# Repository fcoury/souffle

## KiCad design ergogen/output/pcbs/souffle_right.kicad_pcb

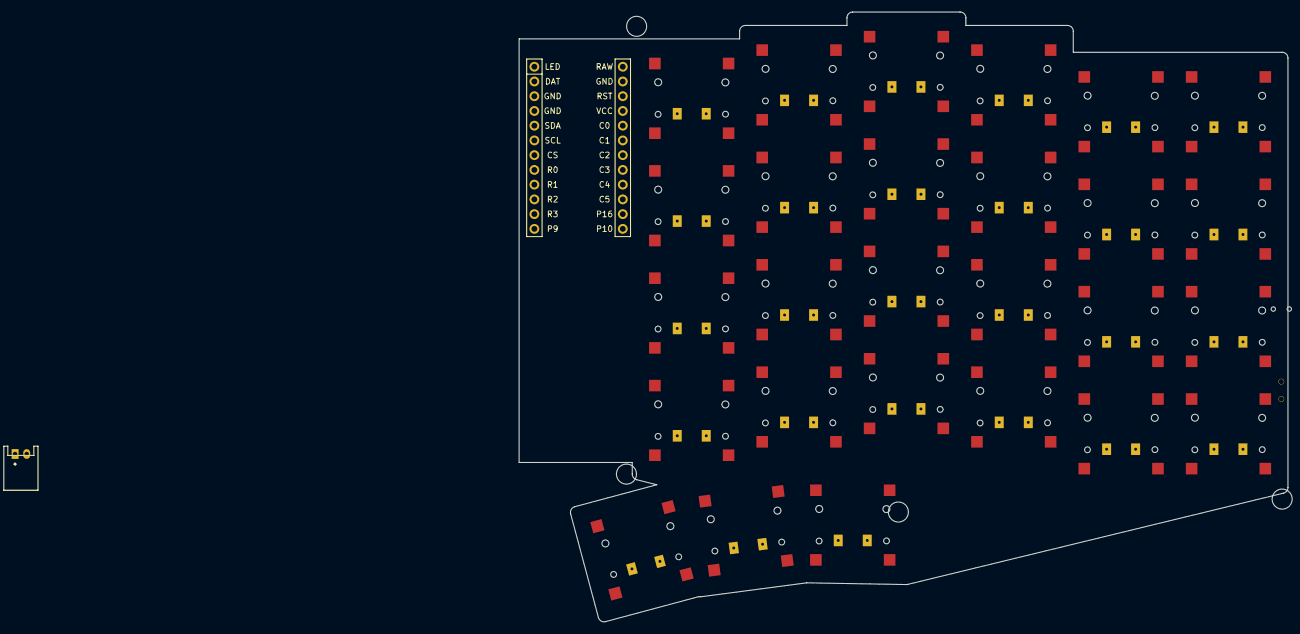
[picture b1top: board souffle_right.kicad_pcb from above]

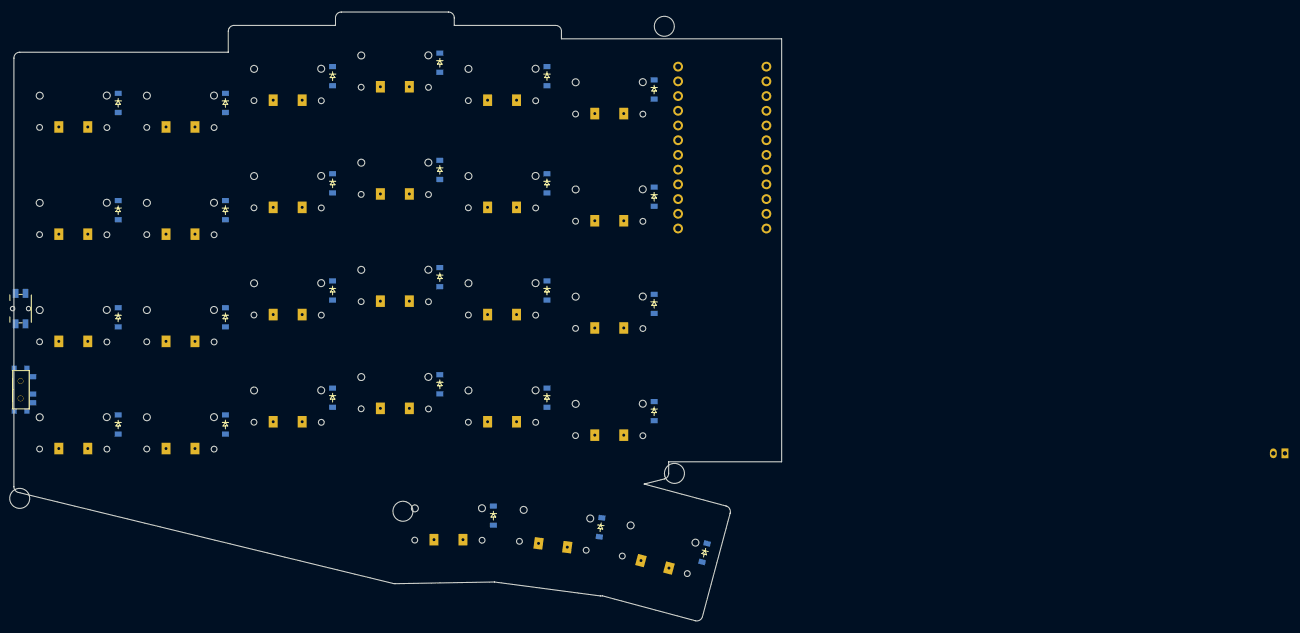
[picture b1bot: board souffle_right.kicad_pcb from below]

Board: 2 copper layers, 132.5 x 105.1 mm, 62 parts (27 on the bottom side), 41 nets, no tracks yet.

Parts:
B1: Panasonic_EVQPUL_EVQPUC
D1, D2, D3, D4, D5, D6, D7, D8, D9, D10, D11, D12, D13, D14, D15, D16, D17, D18, D19, D20, D21, D22, D23, D24, D25, D26, D27: diode_tht_sod123
JST1: JST_PH_S2B-PH-K_02x2.00mm_Angled
MCU1: mcu_nice_nano
MH1, MH2, MH3, MH4: mounting_hole_npth
S1, S2, S3, S4, S5, S6, S7, S8, S9, S10, S11, S12, S13, S14, S15, S16, S17, S18, S19, S20, S21, S22, S23, S24, S25, S26, S27: CPG1316S01D02
T1: SPDT_C128955

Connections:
C0: MCU1.5, S1.1, S2.1, S3.1, S4.1
C1: MCU1.6, S5.1, S6.1, S7.1, S8.1
C2: MCU1.7, S9.1, S10.1, S11.1, S12.1
C3: MCU1.8, S13.1, S14.1, S15.1, S16.1, S25.1
C4: MCU1.9, S17.1, S18.1, S19.1, S20.1, S26.1
C5: MCU1.10, S21.1, S22.1, S23.1, S24.1, S27.1
GND: B1.1, JST1.2, MCU1.2, MCU1.21, MCU1.22
R0: D4.1, D8.1, D12.1, D16.1, D20.1, D24.1, MCU1.17
R1: D3.1, D7.1, D11.1, D15.1, D19.1, D23.1, MCU1.16
R2: D2.1, D6.1, D10.1, D14.1, D18.1, D22.1, MCU1.15
R3: D1.1, D5.1, D9.1, D13.1, D17.1, D21.1, MCU1.14
R4: D25.1, D26.1, D27.1
RAW: MCU1.1, T1.2
RST: B1.2, MCU1.3
mirror_index_bottom: D17.2, S17.2
mirror_index_home: D18.2, S18.2
mirror_index_number: D20.2, S20.2
mirror_index_top: D19.2, S19.2
mirror_inner_bottom: D21.2, S21.2
mirror_inner_home: D22.2, S22.2
mirror_inner_number: D24.2, S24.2
mirror_inner_top: D23.2, S23.2
mirror_inward_home: D25.2, S25.2
mirror_middle_bottom: D13.2, S13.2
mirror_middle_home: D14.2, D26.2, S14.2, S26.2
mirror_middle_number: D16.2, S16.2
mirror_middle_top: D15.2, S15.2
mirror_outer_bottom: D1.2, S1.2
mirror_outer_home: D2.2, S2.2
mirror_outer_number: D4.2, S4.2
mirror_outer_top: D3.2, S3.2
mirror_outward_home: D27.2, S27.2
mirror_pinky_bottom: D5.2, S5.2
mirror_pinky_home: D6.2, S6.2
mirror_pinky_number: D8.2, S8.2
mirror_pinky_top: D7.2, S7.2
mirror_ring_bottom: D9.2, S9.2
mirror_ring_home: D10.2, S10.2
mirror_ring_number: D12.2, S12.2
mirror_ring_top: D11.2, S11.2
pos: JST1.1, T1.1

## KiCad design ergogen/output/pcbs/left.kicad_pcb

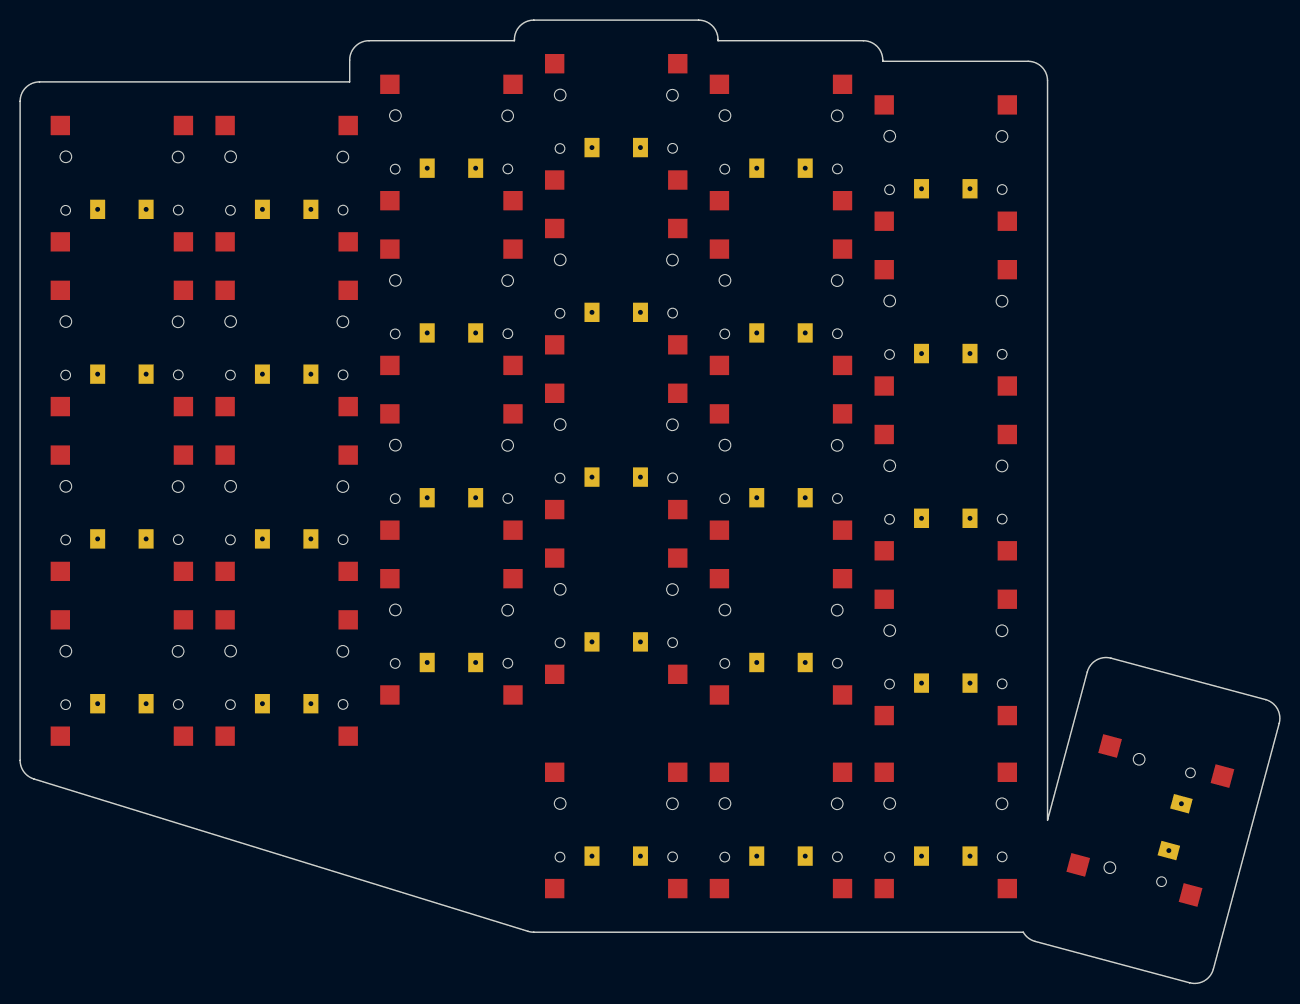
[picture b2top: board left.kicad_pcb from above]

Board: 2 copper layers, 130.0 x 99.4 mm, 28 parts (0 on the bottom side), 6 nets, no tracks yet.

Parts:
S1, S2, S3, S4, S5, S6, S7, S8, S9, S10, S11, S12, S13, S14, S15, S16, S17, S18, S19, S20, S21, S22, S23, S24, S25, S26, S27, S28: CPG1316S01D02_reversible

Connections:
C0: S1.1, S2.1, S3.1, S4.1
C1: S5.1, S6.1, S7.1, S8.1
C2: S9.1, S10.1, S11.1, S12.1, S25.1
C3: S13.1, S14.1, S15.1, S16.1, S26.1
C4: S17.1, S18.1, S19.1, S20.1, S27.1
C5: S21.1, S22.1, S23.1, S24.1, S28.1

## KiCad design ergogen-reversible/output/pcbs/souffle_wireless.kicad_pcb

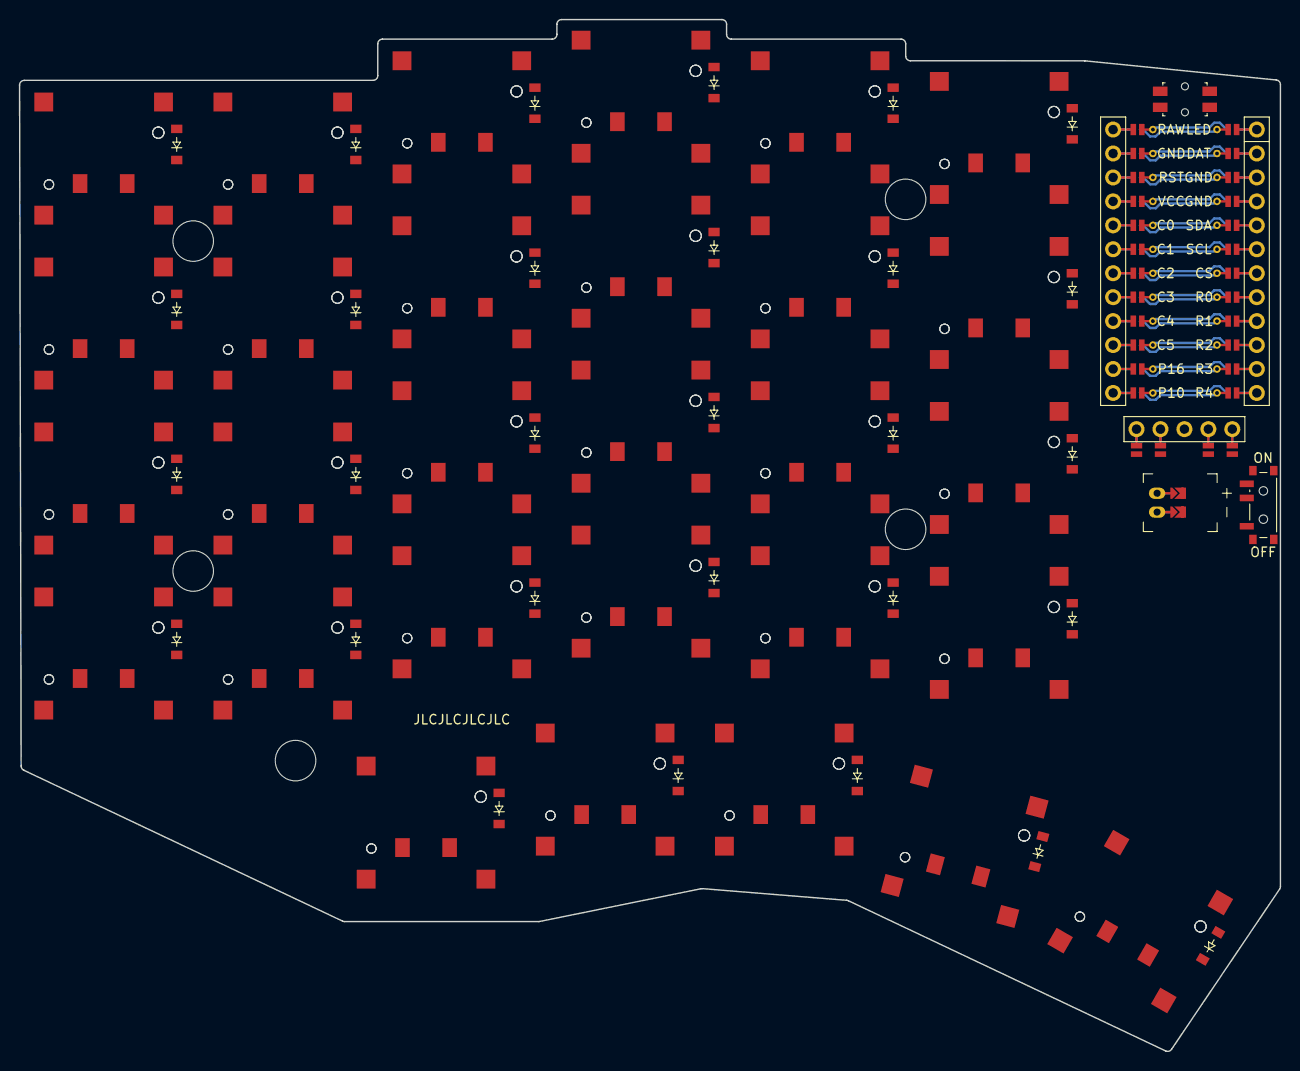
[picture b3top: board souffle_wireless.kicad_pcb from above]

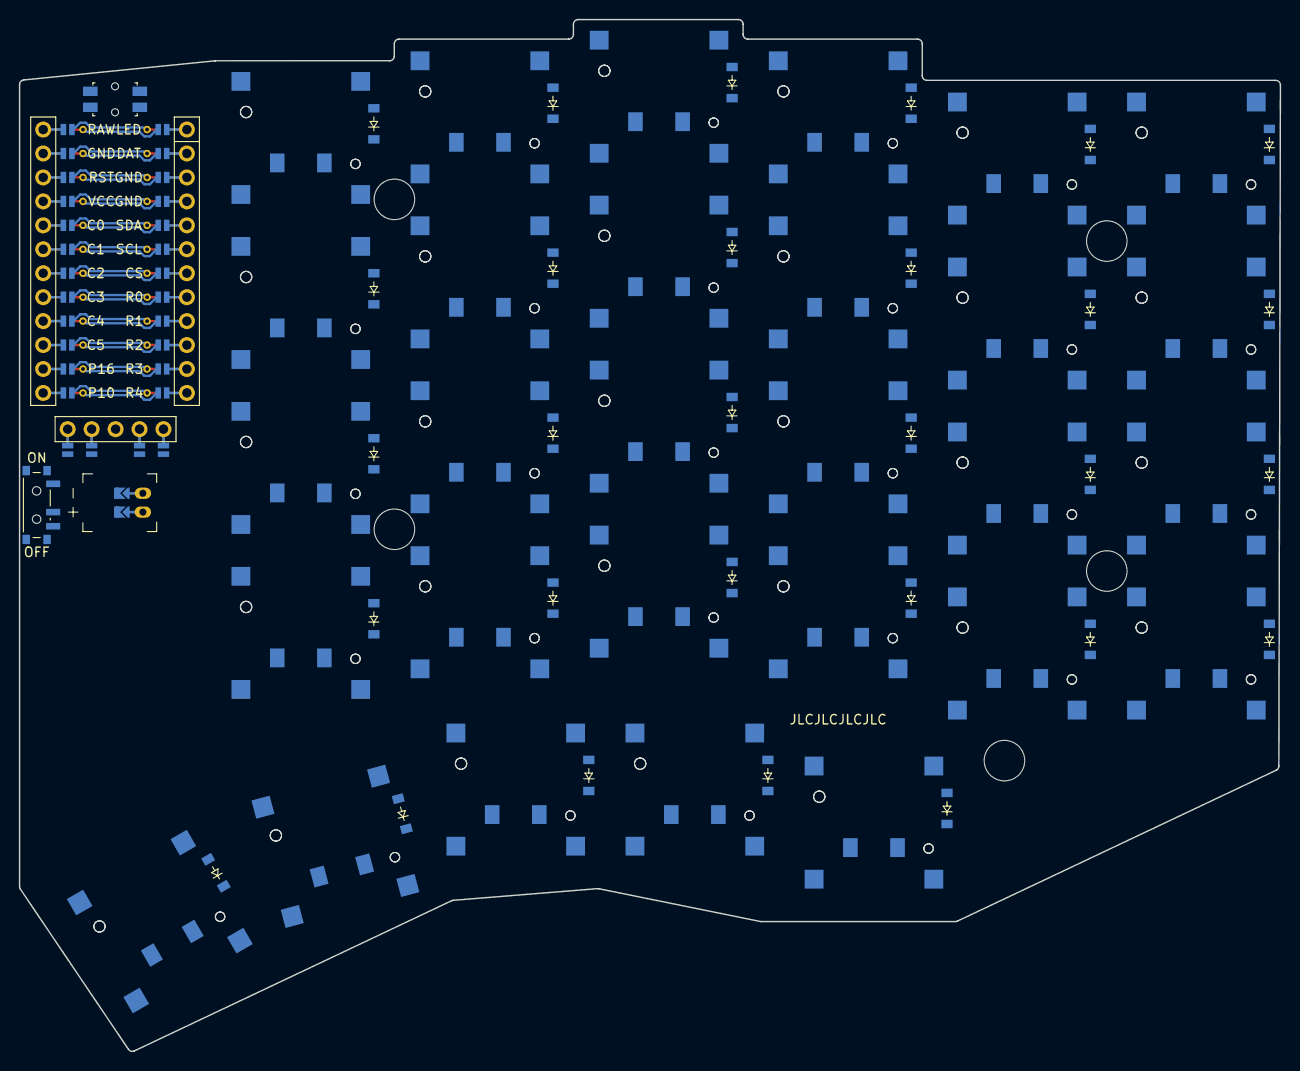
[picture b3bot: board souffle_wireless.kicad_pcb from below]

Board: 2 copper layers, 133.8 x 109.5 mm, 126 parts (58 on the bottom side), 83 nets.

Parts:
D1, D2, D3, D4, D5, D6, D7, D8, D9, D10, D11, D12, D13, D14, D15, D16, D17, D18, D19, D20, D21, D22, D23, D24, D25, D26, D27, D28, D29, D30, D31, D32, D33, D34, D35, D36, D37, D38, D39, D40, D41, D42, D43, D44, D45, D46, D47, D48, D49, D50, D51, D52, D53, D54, D55, D56, D57, D58: diode_tht_sod123
DISP1: display_nice_view
JST1: battery_connector_jst_ph_2
MCU1: mcu_nice_nano
MH1, MH2, MH3, MH4, MH5: mounting_hole_npth
PWR1: power_switch_smd_side
RST1: reset_switch_smd_side
S1, S2, S3, S4, S5, S6, S7, S8, S9, S10, S11, S12, S13, S14, S15, S16, S17, S18, S19, S20, S21, S22, S23, S24, S25, S26, S27, S28, S29, S30, S31, S32, S33, S34, S35, S36, S37, S38, S39, S40, S41, S42, S43, S44, S45, S46, S47, S48, S49, S50, S51, S52, S53, S54, S55, S56, S57, S58: CPG1316S01D02_mikeholscher

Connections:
BAT_P: JST1.1, PWR1.1, PWR1.3
C0: MCU1.120, S1.2, S2.2, S3.2, S4.2, S30.2, S31.2, S32.2, S33.2
C1: MCU1.119, S5.2, S6.2, S7.2, S8.2, S25.2, S34.2, S35.2, S36.2, S37.2, S54.2
C2: MCU1.118, S9.2, S10.2, S11.2, S12.2, S26.2, S38.2, S39.2, S40.2, S41.2, S55.2
C3: MCU1.117, S13.2, S14.2, S15.2, S16.2, S27.2, S42.2, S43.2, S44.2, S45.2, S56.2
C4: MCU1.116, S17.2, S18.2, S19.2, S20.2, S28.2, S46.2, S47.2, S48.2, S49.2, S57.2
C5: MCU1.115, S21.2, S22.2, S23.2, S24.2, S29.2, S50.2, S51.2, S52.2, S53.2, S58.2
CS: DISP1.10, DISP1.20, MCU1.107
DISP1_1: DISP1.1, DISP1.14, DISP1.27
DISP1_2: DISP1.2, DISP1.15, DISP1.26
DISP1_4: DISP1.4, DISP1.16, DISP1.25
DISP1_5: DISP1.5, DISP1.17, DISP1.24
GND: DISP1.11, DISP1.21, JST1.2, MCU1.103, MCU1.104, MCU1.123, RST1.1, RST1.3
JST1_1: JST1.11, JST1.21, JST1.31
JST1_2: JST1.12, JST1.22, JST1.32
R0: D4.1, D8.1, D12.1, D16.1, D20.1, D24.1, D33.1, D37.1, D41.1, D45.1, D49.1, D53.1, MCU1.108
R1: D3.1, D7.1, D11.1, D15.1, D19.1, D23.1, D32.1, D36.1, D40.1, D44.1, D48.1, D52.1, MCU1.109
R2: D2.1, D6.1, D10.1, D14.1, D18.1, D22.1, D31.1, D35.1, D39.1, D43.1, D47.1, D51.1, MCU1.110
R3: D1.1, D5.1, D9.1, D13.1, D17.1, D21.1, D30.1, D34.1, D38.1, D42.1, D46.1, D50.1, MCU1.111
R4: D25.1, D26.1, D27.1, D28.1, D29.1, D54.1, D55.1, D56.1, D57.1, D58.1, MCU1.112
RAW: MCU1.124, PWR1.2
RST: MCU1.122, RST1.2, RST1.4
SCL: DISP1.12, DISP1.22, MCU1.106
SDA: DISP1.13, DISP1.23, MCU1.105
VCC: DISP1.3, MCU1.121
big_outward_home_B: D29.2, S29.1
big_outward_home_F: D58.2, S58.1
extra_outward_home_B: D28.2, S28.1
extra_outward_home_F: D57.2, S57.1
index_bottom_B: D17.2, S17.1
index_bottom_F: D46.2, S46.1
index_home_B: D18.2, S18.1
index_home_F: D47.2, S47.1
index_number_B: D20.2, S20.1
index_number_F: D49.2, S49.1
index_top_B: D19.2, S19.1
index_top_F: D48.2, S48.1
inner_bottom_B: D21.2, S21.1
inner_bottom_F: D50.2, S50.1
inner_home_B: D22.2, S22.1
inner_home_F: D51.2, S51.1
inner_number_B: D24.2, S24.1
inner_number_F: D53.2, S53.1
inner_top_B: D23.2, S23.1
inner_top_F: D52.2, S52.1
inward_home_B: D25.2, S25.1
inward_home_F: D54.2, S54.1
mid_home_B: D26.2, S26.1
mid_home_F: D55.2, S55.1
middle_bottom_B: D13.2, S13.1
middle_bottom_F: D42.2, S42.1
middle_home_B: D14.2, S14.1
middle_home_F: D43.2, S43.1
middle_number_B: D16.2, S16.1
middle_number_F: D45.2, S45.1
middle_top_B: D15.2, S15.1
middle_top_F: D44.2, S44.1
outer_bottom_B: D1.2, S1.1
outer_bottom_F: D30.2, S30.1
outer_home_B: D2.2, S2.1
outer_home_F: D31.2, S31.1
outer_number_B: D4.2, S4.1
outer_number_F: D33.2, S33.1
outer_top_B: D3.2, S3.1
outer_top_F: D32.2, S32.1
outward_home_B: D27.2, S27.1
outward_home_F: D56.2, S56.1
pinky_bottom_B: D5.2, S5.1
pinky_bottom_F: D34.2, S34.1
pinky_home_B: D6.2, S6.1
pinky_home_F: D35.2, S35.1
pinky_number_B: D8.2, S8.1
pinky_number_F: D37.2, S37.1
pinky_top_B: D7.2, S7.1
pinky_top_F: D36.2, S36.1
ring_bottom_B: D9.2, S9.1
ring_bottom_F: D38.2, S38.1
ring_home_B: D10.2, S10.1
ring_home_F: D39.2, S39.1
ring_number_B: D12.2, S12.1
ring_number_F: D41.2, S41.1
ring_top_B: D11.2, S11.1
ring_top_F: D40.2, S40.1

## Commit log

2025-02-05 feat: initial commit
2025-02-06 feat: new footprints
2025-02-06 feat: souffle layout
2025-02-06 chore: ignore KiCad temporary files
2025-02-06 feat: souffle outputs
2025-02-06 fix: number row on top and improved outline
2025-02-06 docs: drawing of the outline
2025-02-06 feat: outline improvements
2025-02-06 feat: GitHub actions for souffle
2025-02-07 feat: LED and switches ratsnest
2025-02-07 feat: fixed pinout
2025-02-07 feat: routing rule for new row, pins and LEDs
2025-02-07 feat: only routes wireless version
2025-02-07 feat: moved on off switch a bit up
2025-02-07 feat: revert moving on off switch
2025-02-07 feat: adjusted the screw hole instead
2025-02-07 feat: outline
2025-02-11 feat: PCB holes alignment
2025-02-12 feat(souffle): initial routed pcb
2025-02-12 fix: don't need extra pins
2025-02-12 feat: redoing with two hands
2025-02-12 feat: sane outline for left pcb
2025-02-12 feat: improved ergogen component names in general
2025-02-12 feat: improved outlines
2025-02-12 feat: refining bottom row
2025-02-12 feat: thumb key 1.5u (thanks @chadtrans)
2025-02-13 feat: diodes and mcu cover
2025-02-13 feat: reset and battery footprints
2025-02-13 feat: CI with left board
2025-02-13 feat: right hand pcb
2025-02-13 feat: both hands working
2025-02-13 feat: autoroute for left and right hands
2025-02-13 feat: choc version
2025-02-14 feat: new thumb cluster
2025-02-14 feat: moved mcu to the back and shortened its supporting tab
2025-02-14 feat: left hand mcu and buttons on the back
2025-02-14 feat: mcu and buttons positioning on the left hand
2025-02-14 feat: mcu and buttons positioning for the right hand
2025-02-15 feat: left hand screw holes
2025-02-28 feat: left hand redesign
2025-02-28 feat: attempt to move mcu to bottom
